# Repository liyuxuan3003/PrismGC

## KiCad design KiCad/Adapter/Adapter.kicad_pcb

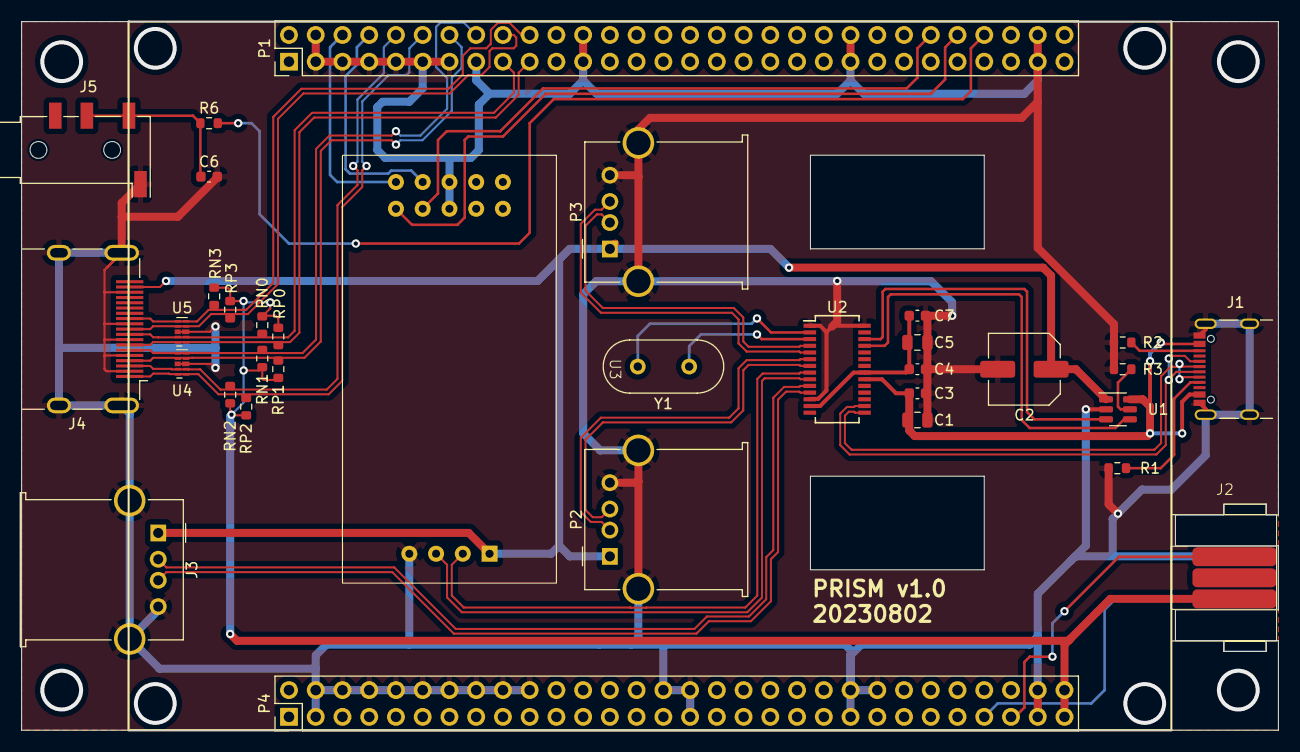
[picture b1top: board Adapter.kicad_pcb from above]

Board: 2 copper layers, 119.4 x 67.3 mm, 34 parts (0 on the bottom side), 38 nets.

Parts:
C1, C5: 10uF; C_0805_2012Metric
C2: 330uF; C_Elec_6.3x5.8
C3, C4, C6: 0.1uF; C_0603_1608Metric
C7: 1uF; C_0603_1608Metric
J1: USB_C_Receptacle; USB_C_Receptacle_GCT_USB4105-xx-A_16P_TopMnt_Horizontal
J2: Nunchunk
J3: USB_A; USB_A_Molex_67643_Horizontal
J4: HDMI_A; HDMI_A_Molex_208658-1001_Horizontal
J5: AudioJack3; Jack_3.5mm_KoreanHropartsElec_PJ-320D-4A_Horizontal
P1, P4: Conn_02x30_Odd_Even_Shielded; PinHeader_2x30_P2.54mm_Vertical
P2, P3: USB_A; USB_A_Molex_67643_Horizontal
R1, R2: 5.1k; R_0603_1608Metric
R3: 47k; R_0603_1608Metric
R6: 2k; R_0603_1608Metric
RN0, RN1, RN2, RN3: 49.9; R_0603_1608Metric
RP0, RP1, RP2, RP3: 49.9; R_0603_1608Metric
U1: CH217K; SOT-23-6
U2: CH334U; SSOP-28_3.9x9.9mm_P0.635mm
U3: DAP
U4, U5: AZ1045-04F; Diodes_UDFN-10_1.0x2.5mm_P0.5mm
Y1: 12MHz; Crystal_HC49-4H_Vertical

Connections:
+3V3: J2.3 (3.3V), P4.59, P4.60, RN0.1, RN1.1, RN2.1, RN3.1, RP0.1, RP1.1, RP2.1, RP3.1
/3v3: C4.2, C5.2, C7.2, U2.13 (VDD33), U2.21 (VDD33)
/BUZ: P1.54, R6.2
/HDMI_CLK_N: J4.12 (CK-), P1.20, RN3.2, U5.5 (Line5), U5.6 (NC)
/HDMI_CLK_P: J4.10 (CK+), P1.18, RP3.2, U5.4 (Line3), U5.7 (NC)
/HDMI_D0_N: J4.9 (D0-), P1.17, RN0.2, U5.2 (Line2), U5.9 (NC)
/HDMI_D0_P: J4.7 (D0+), P1.19, RP0.2, U5.1 (Line1), U5.10 (NC)
/HDMI_D1_N: J4.6 (D1-), P1.16, RN1.2, U4.5 (Line5), U4.6 (NC)
/HDMI_D1_P: J4.4 (D1+), P1.14, RP1.2, U4.4 (Line3), U4.7 (NC)
/HDMI_D2_N: J4.3 (D2-), P1.10, RN2.2, U4.2 (Line2), U4.9 (NC)
/HDMI_D2_P: J4.1 (D2+), P1.12, RP2.2, U4.1 (Line1), U4.10 (NC)
/OVCUR: U1.3 (FLAG#), U2.26 (OVCUR#)
/PWREN: U1.4 (EN#), U2.25 (PWREN#)
/RX: P1.52, U3.1 (RX)
/SCL: J2.6 (SCL), P4.53
/SDA: J2.1 (SDA), P4.55
/SWCLK: P1.6, U3.2 (CLK)
/SWDIO: P1.8, U3.4 (DIO)
/TX: P1.50, U3.3 (TX)
/UP_D+: J1.A6 (D+), J1.B6 (D+), U2.16 (DPU)
/UP_D-: J1.A7 (D-), J1.B7 (D-), U2.15 (DMU)
/USB1_D+: J3.3 (D+), U2.11 (DP1)
/USB1_D-: J3.2 (D-), U2.10 (DM1)
/USB2_D+: U2.9 (DP2), U3.13 (D+)
/USB2_D-: U2.8 (DM2), U3.12 (D-)
/USB3_D+: P2.3 (D+), U2.7 (DP3)
/USB3_D-: P2.2 (D-), U2.6 (DM3)
/USB4_D+: P3.3 (D+), U2.5 (DP4)
/USB4_D-: P3.2 (D-), U2.4 (DM4)
/VBUS_IN: C1.1, C3.2, J1.A4 (VBUS), J1.A9 (VBUS), J1.B4 (VBUS), J1.B9 (VBUS), U1.6 (VIN), U2.20 (V5)
GND: C1.2, C2.2, C3.1, C4.1, C5.1, C6.2, C7.1, J1.A1 (GND), J1.A12 (GND), J1.B1 (GND), J1.B12 (GND), J1.S1 (SHIELD), J2.4 (GND), J3.4 (GND), J3.5 (Shield), J4.2 (D2S), J4.5 (D1S), J4.8 (D0S), J4.11 (CKS), J4.17 (GND), J4.SH, J5.S, P1.3, P1.4, P1.5, P1.7, P1.9, P1.11, P1.13, P1.15, P1.23, P1.24, P1.43, P1.44, P1.57, P1.58, P2.4 (GND), P2.5 (Shield), P3.4 (GND), P3.5 (Shield), P4.3, P4.4, P4.6, P4.8, P4.10, P4.12, P4.14, P4.16, P4.18, P4.20, P4.30, P4.31, P4.32, P4.43, P4.44, P4.46, P4.57, P4.58, R1.2, R2.2, R3.1, U1.2 (GND), U2.1 (GND), U2.12 (GND), U2.28 (GND), U3.5 (GND), U3.6 (GND), U3.14 (GND), U4.3 (GND), U4.8 (GND), U5.3 (GND), U5.8 (GND)
unnamed: C6.1, J5.R1, J5.T, R6.1
unnamed: J1.A5 (CC1), R1.1
unnamed: J1.B5 (CC2), R2.1
unnamed: R3.2, U1.5 (ISET)
unnamed: U2.3 (XI), Y1.1
unnamed: U2.2 (XO), Y1.2
VBUS: C2.1, J3.1 (VBUS), J4.18 (+5V), P2.1 (VBUS), P3.1 (VBUS), U1.1 (VOUT), U3.11 (VBUS)

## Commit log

2023-02-12 初始化提交。
2023-02-12 在资源汇总中添加了一些链接。
2023-02-12 添加了一些链接。
2023-02-21 cyuyan
2023-02-21 first work
2023-02-21 gengxin1.0
2023-02-21 增加了一些菜鸟教程的链接
2023-02-21 更新了Verilog相关教学和流水灯实验链接
2023-02-21 更新了C语言及M0链接
2023-03-10 更新了实验1-3
2023-03-10 增加了一个Hello World
2023-03-10 增加了七段数码管的实验
2023-03-10 修改了gitignore
2023-03-10 增加了hello lyx and lmj！
2023-03-10 新增了一个Hello world！
2023-03-10 增加了一行没用的注释
2023-03-10 将Resource目录更名为Project，作为存储项目文本资料的文件夹，并在Resouce.md添加了一些新的链接。
2023-03-10 新增了任务列表，在其中添加了考试周假期的任务。
2023-03-10 新增了工作流程。
2023-03-10 修复了Workflow.md中的一个小错误
2023-03-10 增加了CortexM0的测试项目
2023-03-10 新建了静态资源目录，添加了M0和M3的硬件代码，添加了硬木课堂M0的教程代码。
2023-03-11 更新了板子链接
2023-03-12 更新了十个数的数值比较器和猜数字游戏
2023-03-13 完成了前三个实验的复习合并和第四个实验的编写优化（已跑通）
2023-03-14 使用了Malloc实现任意数量的数值排序
2023-03-14 新增了第二个M0实验，修正了第一个M0实验中的错误
2023-03-15 完成了M0的实验3
2023-03-15 上传实验五的代码结果
2023-03-15 完成了M0的实验4
2023-03-15 完成实验6的相关内容
2023-03-15 完成了M0的实验8，实现了串口通讯
2023-03-15 新建了M0的Final实验
2023-03-16 做了一些实验
2023-03-16 重整了Final的Verilog代码，添加了注释，删除了不必要的代码
2023-03-16 尝试在Final中添加了软件代码，但未成功
2023-03-16 尝试重新引入了最简汇编代码，并修正了硬件代码AHBlite_Decoder.v中的一个错误
2023-03-16 没啥变化
2023-03-16 加了一些无意义的空格
2023-03-16 修改了Final的启动汇编，新增了GPIO硬件代码
2023-03-16 初步完成了GPIO的引入
2023-03-16 修正了一个小错误
2023-03-16 尝试将GPIO从8位改为32位
2023-03-16 继续修改软硬件代码以适配GPIO
2023-03-16 更新了跑马灯实验和蜂鸣器实验的keil文件和hex等文件
2023-03-16 继续修改代码，但反正没完全工作
2023-03-16 Final的GPIO初步调通，但非对齐访问会崩溃，有待修复
2023-03-17 无显著修改
2023-03-17 GPIO成功跑通
2023-03-17 完成了实验7-9的主要工作，但8 9的连接存在问题 有待进一步完善
2023-03-17 GPIO多通道扩展的尝试，但还有问题
2023-03-17 添加了显示屏的图纸
2023-03-17 GPIO多通道扩展继续尝试，目前单通道能跑通了
2023-03-18 尝试引入七段数码管的硬件驱动
2023-03-18 尝试引入七段数码管的硬件驱动和软件驱动，未成功
2023-03-18 做了些调试，没通
2023-03-18 提交了一份STM32寄存器版本的MDK工程模板
2023-03-18 确认多路GPIO跑通
2023-03-18 M0现在可以正常驱动硬件了
2023-03-18 添加了gitignore项
2023-03-18 项目文件无意义的变化
2023-03-18 更新了HAL库类型的工程建立模板
2023-03-18 更新了自建项目：或运算表决器
2023-03-19 新建了集创赛宣讲记录
2023-03-21 暂不清楚什么时候发生的改动，但保险起见先上传
2023-03-24 引入了有关显示屏和内存的代码样例
2023-03-25 向Final项目中引入了HDMI代码
2023-03-25 调制好了HDMI的代码，但不工作
2023-03-25 尝试将lcd_para中的参数改成1920x1080，但仍然没有解决问题
2023-03-25 增加了手柄相关资料链接
2023-03-25 显示屏好像开始工作了，但似乎不太稳定
2023-03-25 尝试连接了VGA的部分
2023-03-25 无实质更改
2023-03-25 成功的可以显示单种状态
2023-03-28 完成WII的编译
2023-04-01 现在HDMI_DATA及其相关问题被解决
2023-04-01 现在M0可以自由控制显示图案了
2023-04-01 现在M0可以用按键控制显示屏图案了
2023-04-01 引入LCD测试项目
2023-04-01 可以自行创建pll的IP，降低了显示屏的分辨率
2023-04-01 逐步取得对显示器的控制，但仍然有问题
2023-04-01 显示器调试成功
2023-04-01 显示器分辨率改至1024x600
2023-04-01 引入了SDRAM_AS_BRAM的代码
2023-04-02 改了很多东西，反正没啥东西在工作
2023-04-02 引入了SDRAM_VGA的示例
2023-04-02 找到了图案生成的关键代码，优化了它的缩进
2023-04-02 清理了大量无用代码
2023-04-02 显示屏取得控制
2023-04-03 游戏机功能雏形
2023-04-04 游戏内容进行了丰富
2023-04-08 在HDMITest中移除了RAM相关内容
2023-04-08 更换了Final中的HDMI部分
2023-04-08 尝试搞一些显示指令，失败
2023-04-08 显示取得了一些进展，现在可以控制显示屏的局部了
2023-04-09 可以在局部显示，但有怪问题
2023-04-09 改了一些问题，更糟了
2023-04-10 上传已经完成的IIC部分
2023-04-15 简化代码，尚能显示
2023-04-15 现在可以在红色的背景上显示绿色条带
2023-04-15 现在可以在红色的背景上显示花色条带，以最高频率工作
2023-04-15 现在可以显示一个半条带，但是还是散发着诡异的气息
2023-04-15 现在可以以最小32为步长写数据
2023-04-15 现在可以基本实现单像素写
2023-04-15 现在可以动态的调整写入长度，但刷屏速率是3秒
2023-04-15 现在真的好像可以工作了，前一个版本似乎有问题
2023-04-15 去除了不必要的内容，该版本是SDRAM_VGA_Display在挂总线前的最后版本
2023-04-16 将SDRAM_VGA项目并入Final，初步实现M0对显示屏的可控，但尚有两个问题，首先是sys_vaild的读取不成功，其次是分辨率变成了1920x1200。
2023-04-16 现在可用读取到sys_vaild等内容，可以正常绘制，但HDMI的时序似乎有问题，显示屏花的。
2023-04-16 做了些无用的改动
2023-04-16 现在屏幕好像好了？改动是加了个rst_n
2023-04-16 编写了一些C程序进行测试，基本成功，但刷新有问题
2023-04-16 没啥改动的
2023-04-22 修改了Final的main.c使得同时可以绘制两个方块
2023-04-22 上传了最近修改和C++代码
2023-04-22 开始正式项目，但是没工作
2023-04-22 可以正常开启调试，但程序无法运行
2023-04-22 新增了Final的一个副本
2023-04-22 向预期的方向靠近了一点
2023-04-22 向预期的方向又靠近一步
2023-04-24 游戏机初代V1.0
2023-04-29 现在RAM在Interconnect下了
2023-04-29 乱套了2
2023-04-29 将AHBLite级宏定义化
2023-04-29 将HDMI的复位信号标准化，将GPIO置于AHBLiteGPIO下
2023-04-29 将UART置于AHBLiteUART下
2023-04-29 将HDMI置于AHBLiteHDMI下
2023-04-29 变动了顶层架构
2023-04-29 修复了丢失的iopin
2023-04-29 将RAM部分进一步参数化
2023-04-29 修改了AHBLite下的实例名称
2023-04-29 GPIO初步调整成功
2023-04-29 找到一个神奇的片选语法，现在GPIO清楚多了
2023-04-29 取消了M的宏定义，GPIO调试完成
2023-04-29 将外设地址参数化
2023-04-29 将Digit改挂于AHBLite下
2023-04-29 为Digit添加了重置
2023-04-29 UART调试完毕
2023-04-30 引入了开源的HDMI编码
2023-04-30 现在项目可以在新的HDMI下工作了
2023-04-30 修改了main文件使得显示屏在不同颜色间切换
2023-04-30 除了1024x600的分辨率都无法在FinalCopy中运行，删除了相关宏定义
2023-04-30 不稳定的小游戏2
2023-04-30 尝试引入SDRAM as BRAM，未成功
2023-05-01 恢复旧的HDMI_SDRAM
2023-05-01 将GPU接口标准化
2023-05-02 实现了蜂鸣器的M0控制
2023-05-02 键盘功能受M0控制了
2023-05-02 将FinalCopy中的HDMI更换为开源版本
2023-05-02 将开源的HDMI调试稳定
2023-05-03 尝试引入PingPong，但未成功，系统仍然能运作
2023-05-03 约束了部分外设的addrin和addrout，这似乎与SoC工作不稳定有关
2023-05-03 为Buzzer,Digit,UART的addrin和addrout的约束
2023-05-03 切除了部分SDRAM原有的PingPong代码，现在的PingPong初步开始运作
2023-05-03 PingPong开始运作
2023-05-03 继续梳理SDRAM逻辑
2023-05-03 重建PrismGC项目
2023-05-04 错误的游戏
2023-05-07 实现了单像素的显示
2023-05-08 更新了失败的IIC
2023-05-09 贪吃蛇原型机（垃圾代码）
2023-05-11 添加了定时器功能
2023-05-11 错误代码
2023-05-11 调制代码架构，但现在M0运行紊乱
2023-05-11 无效的更改
2023-05-11 实现了一个基本框架代码
2023-05-11 测试了一下定时器，好像有点问题
2023-05-11 5月11日新代码
2023-05-11 修改了GPULite，现在不需要人为指定sys_wr_len了
2023-05-11 修正了main中的问题
2023-05-12 无事发生存个档
2023-05-12 增加了初始页BGM，恢复了血量计分功能
2023-05-13 更新了利用Timer优化开口位置功能
2023-05-17 更新了Level2关卡，完善了游戏内容
2023-05-26 完成了报告
2023-07-02 增加了gitignore以忽略视频文件
2023-07-02 新的IIC代码
2023-07-02 初赛后重新进入工作
2023-07-03 尝试引入I2C的代码，失败
2023-07-04 在C语言层面实现了字符的显示
2023-07-04 整理了部分顶层硬件代码
2023-07-04 将各模块的硬件代码格式化
2023-07-04 移除了部分无用文件，提出了两个GPU相关代码
2023-07-04 进一步移除无用的GPU相关文件
2023-07-04 删除了fifo的包装文件
2023-07-04 将GPU模块中mem的使用参数化
2023-07-04 移除了SDRAM_HDMI_Display，将其内容并入GPU
2023-07-04 将GPU部分整理干净
2023-07-04 将GPUDataControl中的变量名与上级一致化
2023-07-04 修正了若干警告
2023-07-04 修改了WriteFIFO的触发深度至8及其关联值，大幅提示了效率
2023-07-05 尝试将GPUDataControl提至GPU，失败，文件备份至Test/GPUFailed
2023-07-05 将GPU恢复原样
2023-07-05 进一步提高显示速度
2023-07-05 删除了硬件代码一些无用的注释
2023-07-05 增大RAM空间由16KB至32KB
2023-07-05 Pixels缓冲区的大小由16增大至64
2023-07-05 C语言进行了整理
2023-07-05 假期调试完毕
2023-07-07 不知道修改了啥
2023-07-07 开始修改
2023-07-07 开始了方块的测试
2023-07-07 测试绘图
2023-07-07 编写了一个地图绘制的Demo
2023-07-07 合并后完成了地图Demo的渲染
2023-07-07 “更正格式”
2023-07-07 上传了主角的画法和第一关内容
2023-07-07 实现了字符缩放，但最多两倍，三倍会出问题
2023-07-07 画出起点、终点和陷阱方块
2023-07-07 合并后做了一些修改
2023-07-07 尝试引入LCDPrintf，失败
2023-07-07 增加了按键控制方块移动功能
2023-07-07 增加了只能在冰块上行走的功能，但尚需改进
2023-07-07 加入了LCDPrintf，将主角的绘制代码规范化
2023-07-07 优化了上下左右的移动
2023-07-07 造成了一定的错误
2023-07-07 完成了lmj设计关卡的录入和起始位置选择（未制作具有选择关卡功能的副本）
2023-07-08 奇怪的不知道哪里来的修改
2023-07-08 完善了移动功能
2023-07-08 上传了启动页和选关菜单的代码
2023-07-08 实现了文字和主角的多倍放大
2023-07-08 项目文件的无效修改
2023-07-09 合并lmj的分支，修改了一个错误
2023-07-09 优化了菜单界面
2023-07-09 未完成的移动改进
2023-07-10 修复异常修改
2023-07-10 优化了史莱姆图像
2023-07-10 重新提交菜单页面
2023-07-10 修正了菜单界面的问题，将菜单和游戏连接起来
2023-07-10 完成了启动页和选关菜单的基本工作
2023-07-10 还需要完善的移动
2023-07-11 现在可以用手柄控制游戏了
2023-07-11 暂时改回用按键控制
2023-07-11 到终点时可以进行换页
2023-07-11 画了个苹果并放到了启动页上
2023-07-11 完善了移动，增加了不完整的结算页面
2023-07-12 引入了GetKey()统一手柄和按键操作
2023-07-12 首页上也可以用手柄进入菜单了
2023-07-12 完成了第一关苹果的显示和吃苹果判定
2023-07-12 增加了END页面
2023-07-12 修复了一个在边缘移动出错的bug
2023-07-12 尝试修复PageMazeGame，未成功
2023-07-12 完成对zy的分支
2023-07-12 关闭了手柄操作
2023-07-12 完善了end页面
2023-07-12 进行有关终点的测试
2023-07-12 初步完成主角和苹果的调色盘
2023-07-12 有缺陷的规定方向方块
2023-07-13 完成了当前characters的调色盘并新增了白色箭头
2023-07-13 完善了移动方块，改进了end页面，绘制了右箭头，但存在问题
2023-07-13 合并lmj的分支
2023-07-14 审阅了代码
2023-07-14 现在折射方块可以正常工作了
2023-07-14 稍有改进
2023-07-14 合并了zy的代码
2023-07-14 增加了level2
2023-07-14 删除了GPULite中的一个无用的注释
2023-07-14 修复了显示地图时写死level1的问题
2023-07-14 修复了箭头绘制的问题 并且新增控制箭头颜色的参数
2023-07-14 修复了左右箭头不对称的问题
2023-07-14 优化了调色盘方案的实现
2023-07-14 END又双叒叕出bug了
2023-07-14 修复了level2无法正常结束的问题
2023-07-14 完成了碎石的显示部分，并且改用点画矩形
2023-07-14 增加了level2和level3
2023-07-14 调试管卡
2023-07-14 优化了冰块的显示
2023-07-14 改进了level1
2023-07-14 修改了首页
2023-07-14 将RamWrite由udelay(5)改为ndelay(1000)，但End界面再次会消失
2023-07-14 修复了End界面消失的问题
2023-07-14 继续调试
2023-07-14 关卡更新至level10
2023-07-14 实现了碎石块
2023-07-14 现在GetKey()在手柄没有接入时也能正常工作了
2023-07-14 令PageMenu能记住上一次选中的关卡
2023-07-14 引入传送门方块
2023-07-15 增加至level16
2023-07-15 引入了传送门
2023-07-15 完成17-20关的关卡和传送门显示的修改
2023-07-15 合并zy的分支
2023-07-15 增加了lmj游戏的注释
2023-07-16 修复了传送门的bug
2023-07-16 level21
2023-07-16 修改答案位置
2023-07-16 完成了关卡28-32的设计
2023-07-16 更新至level27
2023-07-16 更新音效
2023-07-16 新增了复赛文档
2023-07-17 更新了Menu界面的音效
2023-07-17 完成了游戏介绍的文字部分
2023-07-17 设想了部分答辩问题并上传了元素图片
2023-07-17 引入了绘制地图的程序
2023-07-18 新增了lmj关卡的答案
2023-07-20 任意键进入游戏菜单
2023-07-21 完成文档
2023-07-21 修复了一个小问题
2023-07-21 新建了演讲稿
2023-07-28 增加了TRP方块
2023-07-30 完成了机关门及其开关动效的绘制
2023-07-30 更新了机关
2023-08-01 绘制了陷阱方块，并通过测试
2023-08-01 进一步完善了机关
2023-08-01 完善了机关，单支switch语句已修改为if语句
2023-08-06 稍作修改
2023-08-06 自制板卡
2023-08-06 动画和机关合并完毕
2023-08-07 完成对应状态按钮的绘制，并尝试加入画圆的函数
2023-08-08 优化了画圆算法 同步了关卡中开关函数（备注：主界面画的圆中心裂开了 但关卡不受影响）
2023-08-08 修复了一些问题
2023-08-08 更新了关卡33和关卡34
2023-08-12 完成了33到46关的设计
2023-08-12 完成机加工文件
2023-08-12 修复了内存的问题
2023-08-13 尝试修改硬件RAM配置
2023-08-14 改用BRAM32k实现程序空间
2023-08-14 现在BRAM32k的程序空间扩大到64KB，修正printf的一个错误
2023-08-14 现在可以脱离电源工作
2023-08-14 乱七八糟的烂摊子
2023-08-14 TD版本升级到5.0.5，恢复稳定
2023-08-14 没啥修改
2023-08-14 大量修改，现在勉强可以稳定运行
2023-08-14 又做了些修改
2023-08-15 完成了关卡的初步设计
2023-08-16 修复了栅栏门的bug
2023-08-16 分支合并完成
2023-08-16 优化显示
2023-08-16 完成了33-35关的重新设计 优化了苹果、陷阱的显示
2023-08-16 修复了启动页面方块显示异常的问题
2023-08-16 完成了失败页面的颜色调整
2023-08-16 调整了菜单页面的色彩
2023-08-17 硬件上支持了3.5mm音频输出
2023-08-17 现在可以切换音频输出了
2023-08-17 现在可以接受14个音高了
2023-08-17 绘制了云彩 优化了启动页面显示 并尝试修改菜单和游戏页背景
2023-08-17 更新end界面两首bgm
2023-08-17 调整手柄的交互
2023-08-17 更新了致爱丽丝
2023-08-17 完成合并
2023-08-18 新增了决赛报告
2023-08-19 完成决赛PPT
